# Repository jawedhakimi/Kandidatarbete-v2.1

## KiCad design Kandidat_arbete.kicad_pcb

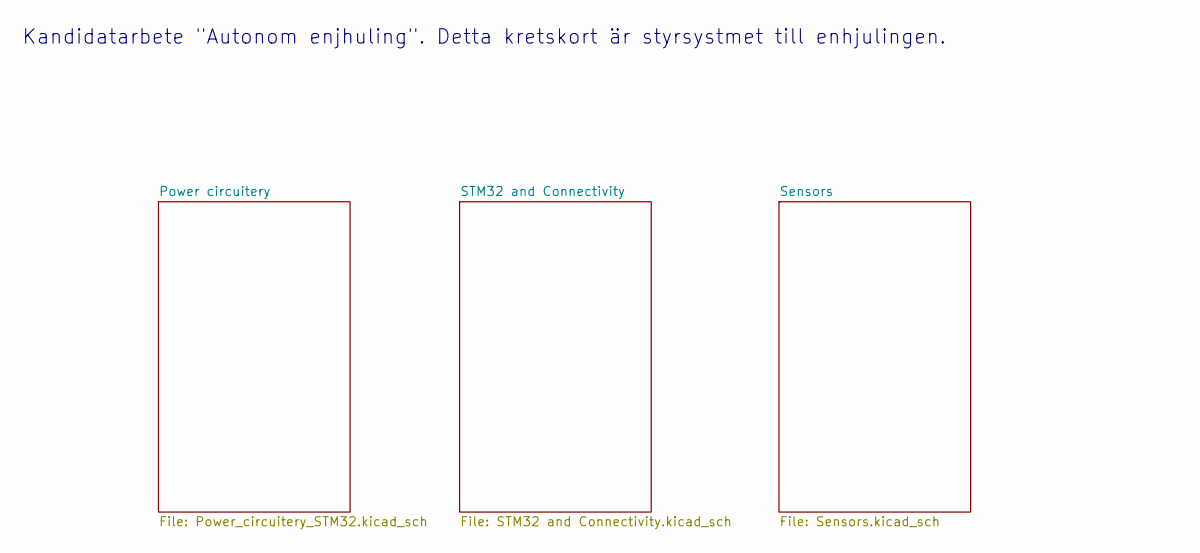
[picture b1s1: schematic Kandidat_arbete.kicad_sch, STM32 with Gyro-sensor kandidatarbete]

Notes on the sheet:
Kandidatarbete "Autonom enjhuling". Detta kretskort är styrsystmet till enhjulingen.

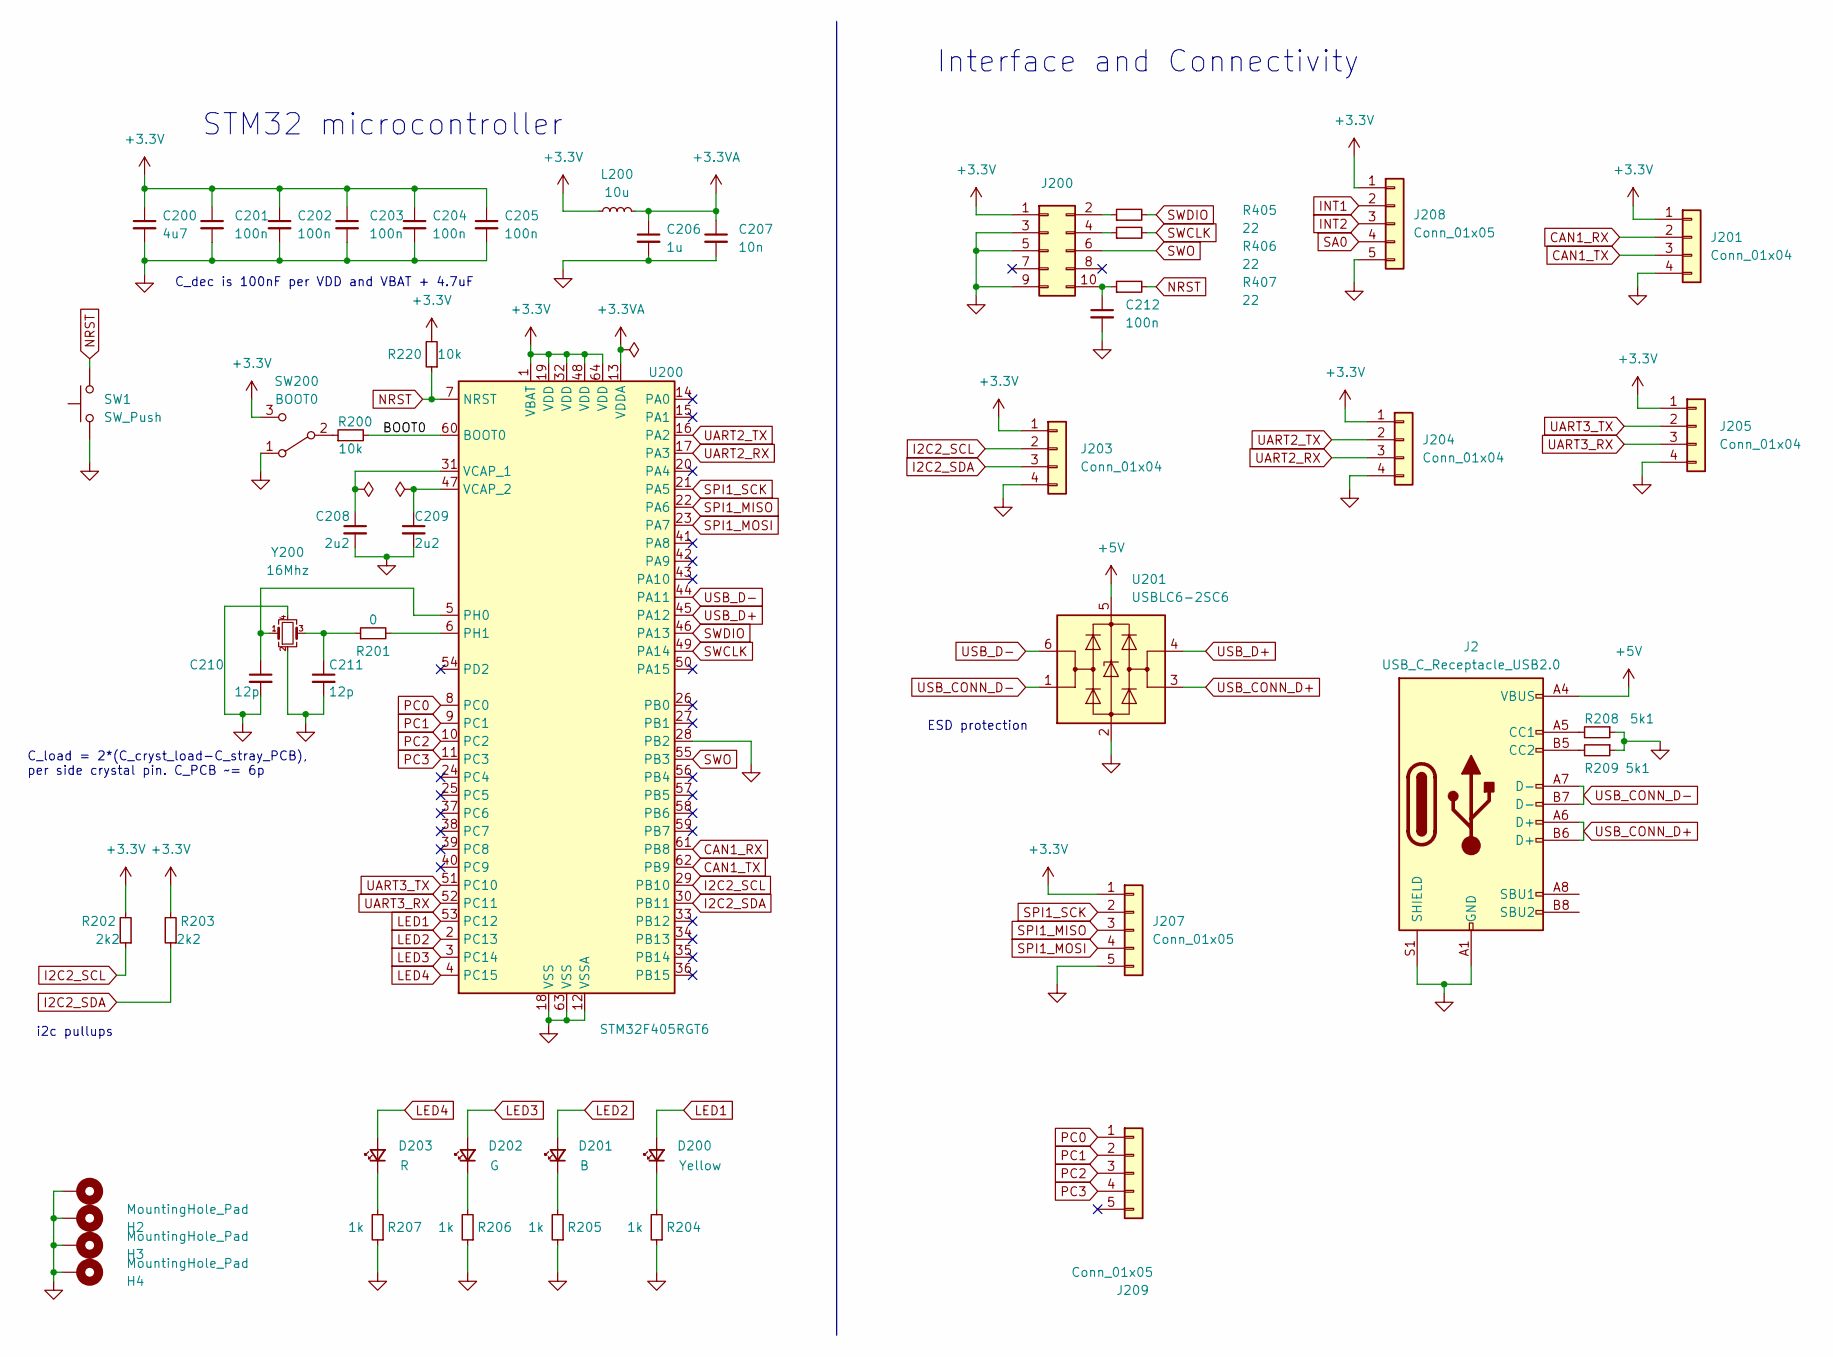
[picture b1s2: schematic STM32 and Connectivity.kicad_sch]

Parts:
C200: 4u7; C_0805_2012Metric; PARTREV C29823; JLC C29823
C201, C202, C203, C204, C205, C212: 100n; C_0805_2012Metric; PARTREV C14663
C206: 1u; C_0805_2012Metric; PARTREV C15849
C207: 10n; C_0805_2012Metric; PARTREV C57112
C208, C209: 2u2; C_0603_1608Metric; PARTREV C23630
C210, C211: 12p; C_0805_2012Metric; PARTREV C38523
D200: Yellow; LED_0603_1608Metric; PARTREV C84256
D201: B; LED_0603_1608Metric; PARTREV C84256
D202: G; LED_0603_1608Metric; PARTREV C84256
D203: R; LED_0603_1608Metric; PARTREV C84256
H1, H2, H3, H4: MountingHole_Pad; MountingHole_3.2mm_M3_Pad_Via
J2: USB_C_Receptacle_USB2.0; GCT_USB4105-GF-A
J200: Conn_02x05_Odd_Even; PinSocket_2x05_P2.54mm_Vertical
J201, J203, J204, J205: Conn_01x04; PinSocket_1x04_P2.54mm_Vertical
J207, J208, J209: Conn_01x05; PinSocket_1x05_P2.54mm_Vertical
L200: 10u; L_0805_2012Metric_Pad1.05x1.20mm_HandSolder; PARTREV C1051; Mouser 710-742792151
R200, R220: 10k; R_0603_1608Metric; PARTREV C25804
R201: 0; R_0603_1608Metric; PARTREV C22764
R202, R203: 2k2; R_0603_1608Metric; PARTREV C23162
R204, R205, R206, R207: 1k; R_0603_1608Metric; PARTREV C25804
R208, R209: 5k1; R_0603_1608Metric; PARTREV C25804
R405, R406, R407: 22; R_0603_1608Metric; PARTREV C227717
SW1: SW_Push; SW_SKRPACE010
SW200: BOOT0; SW_SPDT_PCM12
U200: STM32F405RGT6; LQFP-64_10x10mm_P0.5mm; PARTREV C15742; Mouser 511-STM32F405RGT6
U201: USBLC6-2SC6; SOT-23-6; PARTREV C5261088; Mouser 511-USBLC6-2SC6
Y200: 16Mhz; Crystal_SMD_3225-4Pin_3.2x2.5mm; PARTREV C13738; Mouser 815-ASEAIG-16MHZ-CST

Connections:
+3.3V: C200.1, C201.1, C202.1, C203.1, C204.1, C205.1, J200.1, J201.1, J203.1, J204.1, J205.1, J207.1, J208.1, L200.1, R202.2, R203.2, R220.2, SW200.3 (C), U200.1 (VBAT), U200.19 (VDD), U200.32 (VDD), U200.48 (VDD), U200.64 (VDD); also elsewhere on the board
+3.3VA: C206.1, C207.1, L200.2, U200.13 (VDDA)
+5V: J2.A4 (VBUS), J2.A9 (VBUS), J2.B4 (VBUS), J2.B9 (VBUS), U201.5 (VBUS); also elsewhere on the board
/STM32 and Connectivity/BOOT0: R200.2, U200.60 (BOOT0)
CAN1_RX: J201.2, U200.61 (PB8)
CAN1_TX: J201.3, U200.62 (PB9)
GND: C200.2, C201.2, C202.2, C203.2, C204.2, C205.2, C206.2, C207.2, C208.2, C209.2, C210.2, C211.2, C212.2, H1.1, H2.1, H3.1, H4.1, J2.A1 (GND), J2.A12 (GND), J2.B1 (GND), J2.B12 (GND), J2.S1 (SHIELD), J200.3, J200.5, J200.9, J201.4, J203.4, J204.4, J205.4, J207.5, J208.5, R204.1, R205.1, R206.1, R207.1, R208.1, R209.1, SW1.1, SW200.1 (A), U200.12 (VSSA), U200.18 (VSS), U200.28 (PB2), U200.63 (VSS), U201.2 (GND), Y200.2, Y200.4; also elsewhere on the board
I2C2_SCL: J203.2, R202.1, U200.29 (PB10); also elsewhere on the board
I2C2_SDA: J203.3, R203.1, U200.30 (PB11); also elsewhere on the board
INT1: J208.2; also elsewhere on the board
INT2: J208.3; also elsewhere on the board
LED1: D200.2 (A), U200.53 (PC12)
LED2: D201.2 (A), U200.2 (PC13)
LED3: D202.2 (A), U200.3 (PC14)
LED4: D203.2 (A), U200.4 (PC15)
NRST: R220.1, R407.2, SW1.2, U200.7 (NRST)
unnamed: C208.1, U200.31 (VCAP_1)
unnamed: C209.1, U200.47 (VCAP_2)
unnamed: C211.1, R201.1, Y200.3
unnamed: D200.1 (K), R204.2
unnamed: D201.1 (K), R205.2
unnamed: D202.1 (K), R206.2
unnamed: D203.1 (K), R207.2
unnamed: J2.A5 (CC1), R208.2
unnamed: J2.B5 (CC2), R209.2
unnamed: J200.2, R405.1
unnamed: J200.4, R406.1
unnamed: C212.1, J200.10, R407.1
unnamed: R200.1, SW200.2 (B)
unnamed: C210.1, U200.5 (PH0), Y200.1
unnamed: R201.2, U200.6 (PH1)
PC0: J209.1, U200.8 (PC0)
PC1: J209.2, U200.9 (PC1)
PC2: J209.3, U200.10 (PC2)
PC3: J209.4, U200.11 (PC3)
SA0: J208.4; also elsewhere on the board
SPI1_MISO: J207.3, U200.22 (PA6)
SPI1_MOSI: J207.4, U200.23 (PA7)
SPI1_SCK: J207.2, U200.21 (PA5)
SWCLK: R406.2, U200.49 (PA14)
SWDIO: R405.2, U200.46 (PA13)
SWO: J200.6, U200.55 (PB3)
UART2_RX: J204.3, U200.17 (PA3)
UART2_TX: J204.2, U200.16 (PA2)
UART3_RX: J205.3, U200.52 (PC11)
UART3_TX: J205.2, U200.51 (PC10)
USB_CONN_D+: J2.A6 (D+), J2.B6 (D+), U201.3 (I/O2)
USB_CONN_D-: J2.A7 (D-), J2.B7 (D-), U201.1 (I/O1)
USB_D+: U200.45 (PA12), U201.4 (I/O2)
USB_D-: U200.44 (PA11), U201.6 (I/O1)

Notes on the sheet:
Interface and Connectivity
i2c pullups
C_load = 2*(C_cryst_load-C_stray_PCB), per side crystal pin. C_PCB ~= 6p
ESD protection
STM32 microcontroller
C_dec is 100nF per VDD and VBAT + 4.7uF

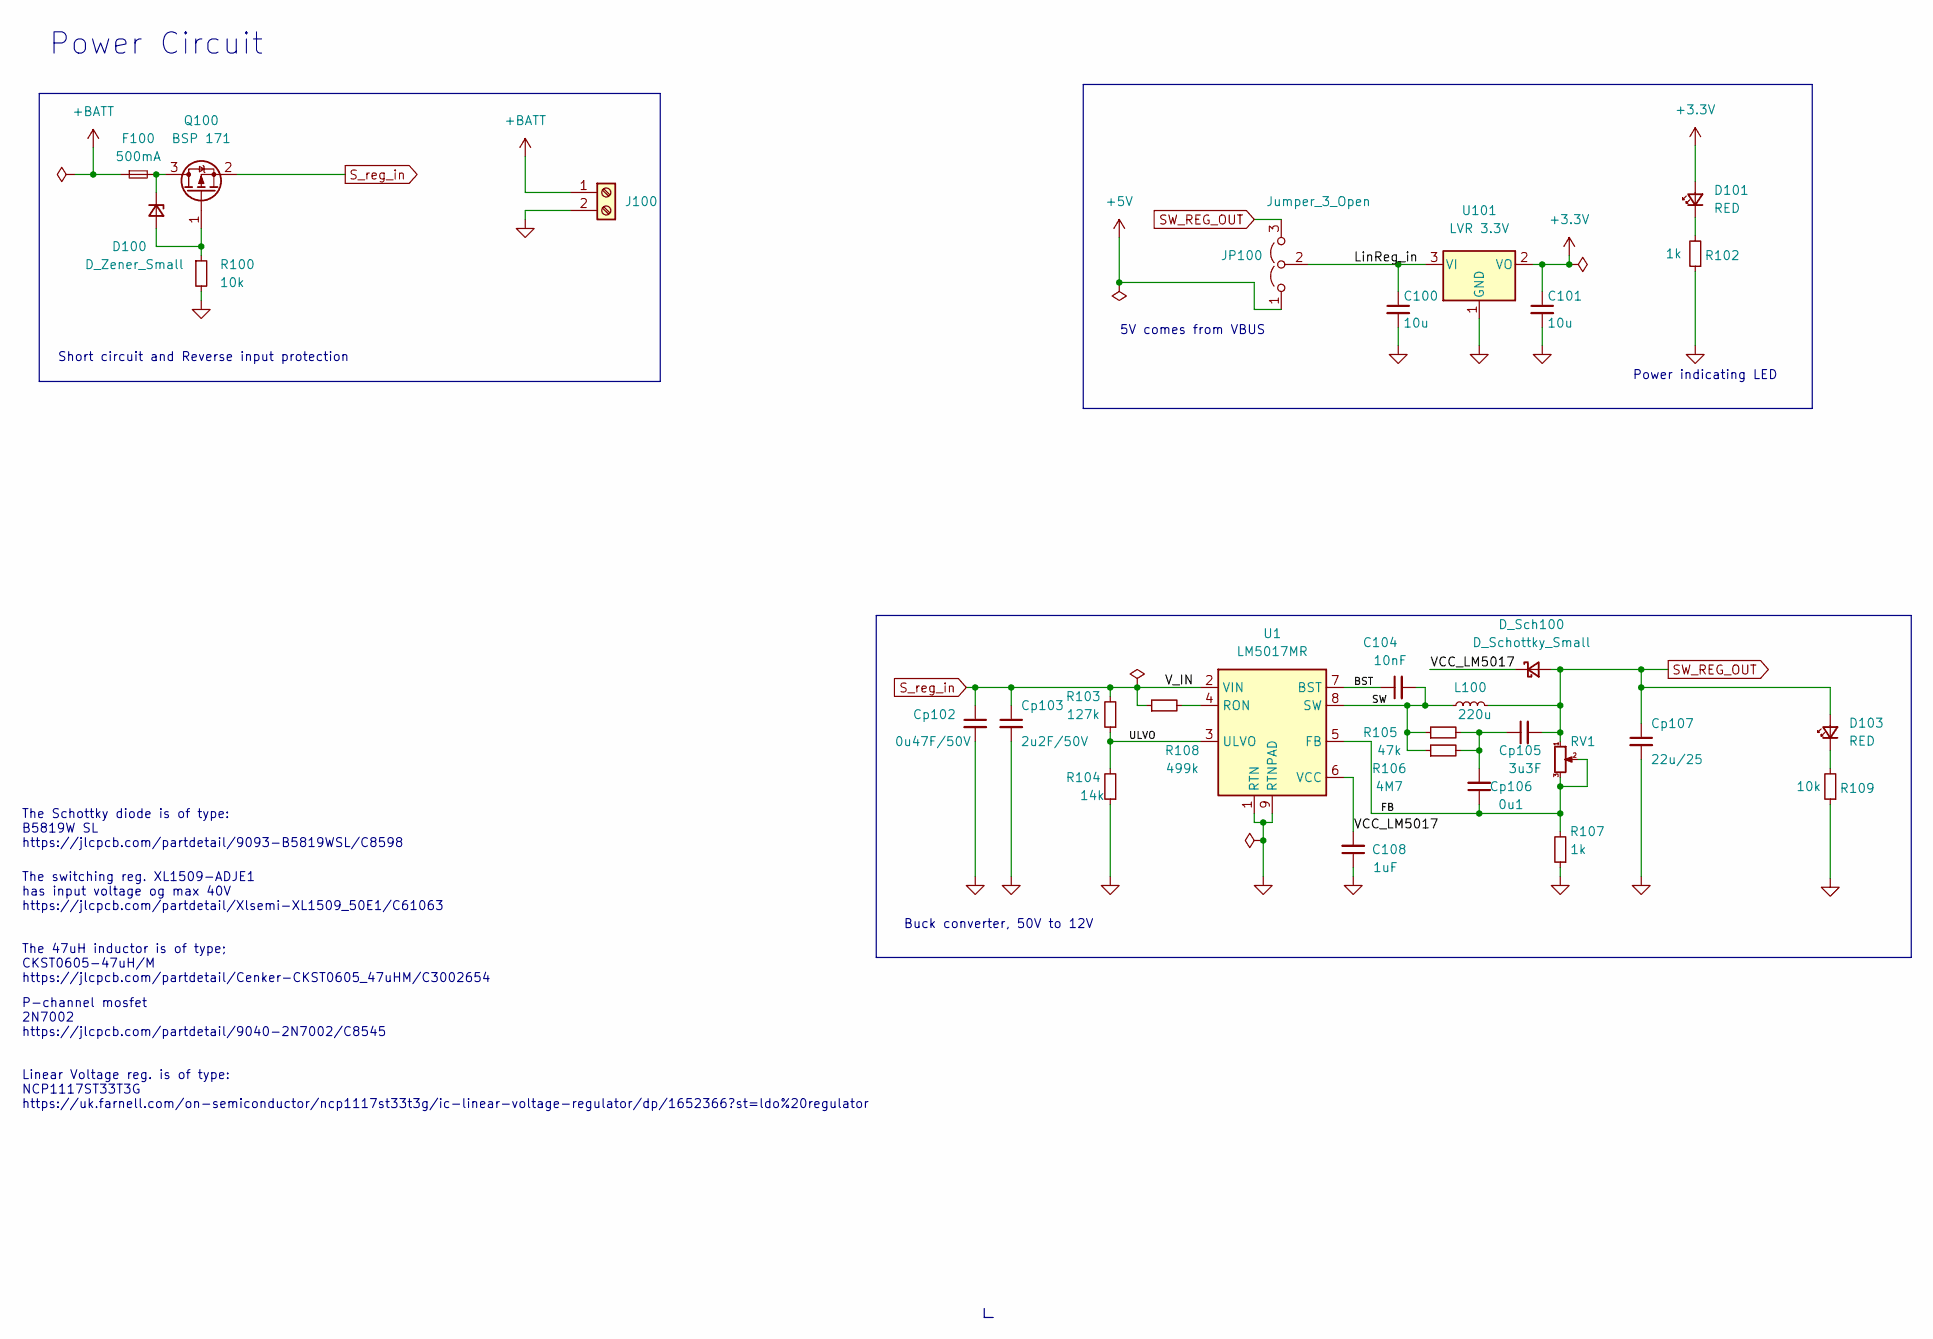
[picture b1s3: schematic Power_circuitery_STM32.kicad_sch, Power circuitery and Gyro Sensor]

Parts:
C100, C101: 10u; C_0805_2012Metric; PARTREV C96446; JLC C96446
C104: 10nF; C_0805_2012Metric; PARTREV C57112
C108: 1uF; C_0805_2012Metric; PARTREV C28323
Cp102: 0u47F/50V; C_0805_2012Metric; PARTREV C13967
Cp103: 2u2F/50V; C_0805_2012Metric; PARTREV C49217
Cp105: 3u3F; C_0805_2012Metric; PARTREV C338093
Cp106: 0u1; C_0805_2012Metric; PARTREV C14663
Cp107: 22u/25; C_0805_2012Metric_Pad1.18x1.45mm_HandSolder; PARTREV C45783
D100: D_Zener_Small; R_Axial_DIN0204_L3.6mm_D1.6mm_P5.08mm_Vertical; PARTREV C8062
D101, D103: RED; LED_0603_1608Metric; PARTREV C84256
D_Sch100: D_Schottky_Small; TO-277; PARTREV C8678; Mouser 637-SK35SMA
F100: 500mA; R_Axial_DIN0204_L3.6mm_D1.6mm_P5.08mm_Vertical; PARTREV C8678
J100: Screw_Terminal_01x02; TerminalBlock_Philmore_TB132_1x02_P5.00mm_Horizontal
JP100: Jumper_3_Open; PinHeader_1x03_P2.54mm_Vertical
L100: 220u; L_Bourns_SRR1208_12.7x12.7mm; PARTREV C2929503; Mouser 652-SRR1208-221KL
Q100: BSP 171; bsp171; PARTREV C15127; Mouser 726-BSP171PH6327
R100: 10k; R_0603_1608Metric; PARTREV C25804
R102: 1k; R_0603_1608Metric; PARTREV C22764
R103: 127k; R_0603_1608Metric; PARTREV C25804
R104: 14k; R_0603_1608Metric; PARTREV C25804
R105: 47k; R_0603_1608Metric; PARTREV C25804
R106: 4M7; R_0603_1608Metric; PARTREV C25804
R107: 1k; R_0603_1608Metric; PARTREV C25804
R108: 499k; R_0603_1608Metric; PARTREV C25804
R109: 10k; R_0603_1608Metric; PARTREV C22764
RV1: R_Potentiometer_Small; TRIM_TC33X-2-103E
U1: LM5017MR; SOIC-8-1EP_3.9x4.9mm_P1.27mm_EP2.95x4.9mm_Mask2.71x3.4mm_Th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; PARTREV C34355; Mouser 926-LM5017MRX/NOPB
U101: LVR 3.3V; SOT-223-3_TabPin2; PARTREV C277892; Mouser 584-ADP3338AKCZ3.3R

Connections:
+3.3V: C101.1, D101.2 (A), U101.2 (VO); also elsewhere on the board
+5V: JP100.1 (A); also elsewhere on the board
+BATT: F100.1, J100.1
/Power circuitery/BST: C104.1, U1.7 (BST)
/Power circuitery/FB: Cp106.1, R107.2, RV1.2, RV1.3, U1.5 (FB)
/Power circuitery/LinReg_in: C100.1, JP100.2 (C), U101.3 (VI)
/Power circuitery/SW: C104.2, L100.1, R105.1, R106.1, U1.8 (SW)
/Power circuitery/ULVO: R103.1, R104.2, U1.3 (ULVO)
/Power circuitery/VCC_LM5017: C108.2, D_Sch100.3 (K), U1.6 (VCC)
GND: C100.2, C101.2, C108.1, Cp102.2, Cp103.2, Cp107.2, J100.2, R100.2, R102.1, R104.1, R107.1, R109.1, U1.1 (RTN), U1.9 (RTNPAD), U101.1 (GND); also elsewhere on the board
unnamed: Cp105.1, Cp106.2, R105.2, R106.2
unnamed: D100.2 (A), Q100.1 (G), R100.1
unnamed: D100.1 (K), F100.2, Q100.3 (D)
unnamed: D101.1 (K), R102.2
unnamed: D103.1 (K), R109.2
unnamed: R108.2, U1.4 (RON)
SW_REG_OUT: Cp105.2, Cp107.1, D103.2 (A), D_Sch100.1 (A), D_Sch100.2 (A), JP100.3 (B), L100.2, RV1.1
S_reg_in: Cp102.1, Cp103.1, Q100.2 (S), R103.2, R108.1, U1.2 (VIN)

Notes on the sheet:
Buck converter, 50V to 12V
5V comes from VBUS
Power Circuit
The Schottky diode is of type: B5819W SL https://jlcpcb.com/partdetail/9093-B5819WSL/C8598
The switching reg. XL1509-ADJE1 has input voltage og max 40V https://jlcpcb.com/partdetail/Xlsemi-XL1509_50E1/C61063
Linear Voltage reg. is of type: NCP1117ST33T3G https://uk.farnell.com/on-semiconductor/ncp1117st33t3g/ic-linear-voltage-regulator/dp/1652366?st=ldo%20regulator
Power indicating LED
Short circuit and Reverse input protection
P-channel mosfet 2N7002 https://jlcpcb.com/partdetail/9040-2N7002/C8545
The 47uH inductor is of type; CKST0605-47uH/M https://jlcpcb.com/partdetail/Cenker-CKST0605_47uHM/C3002654

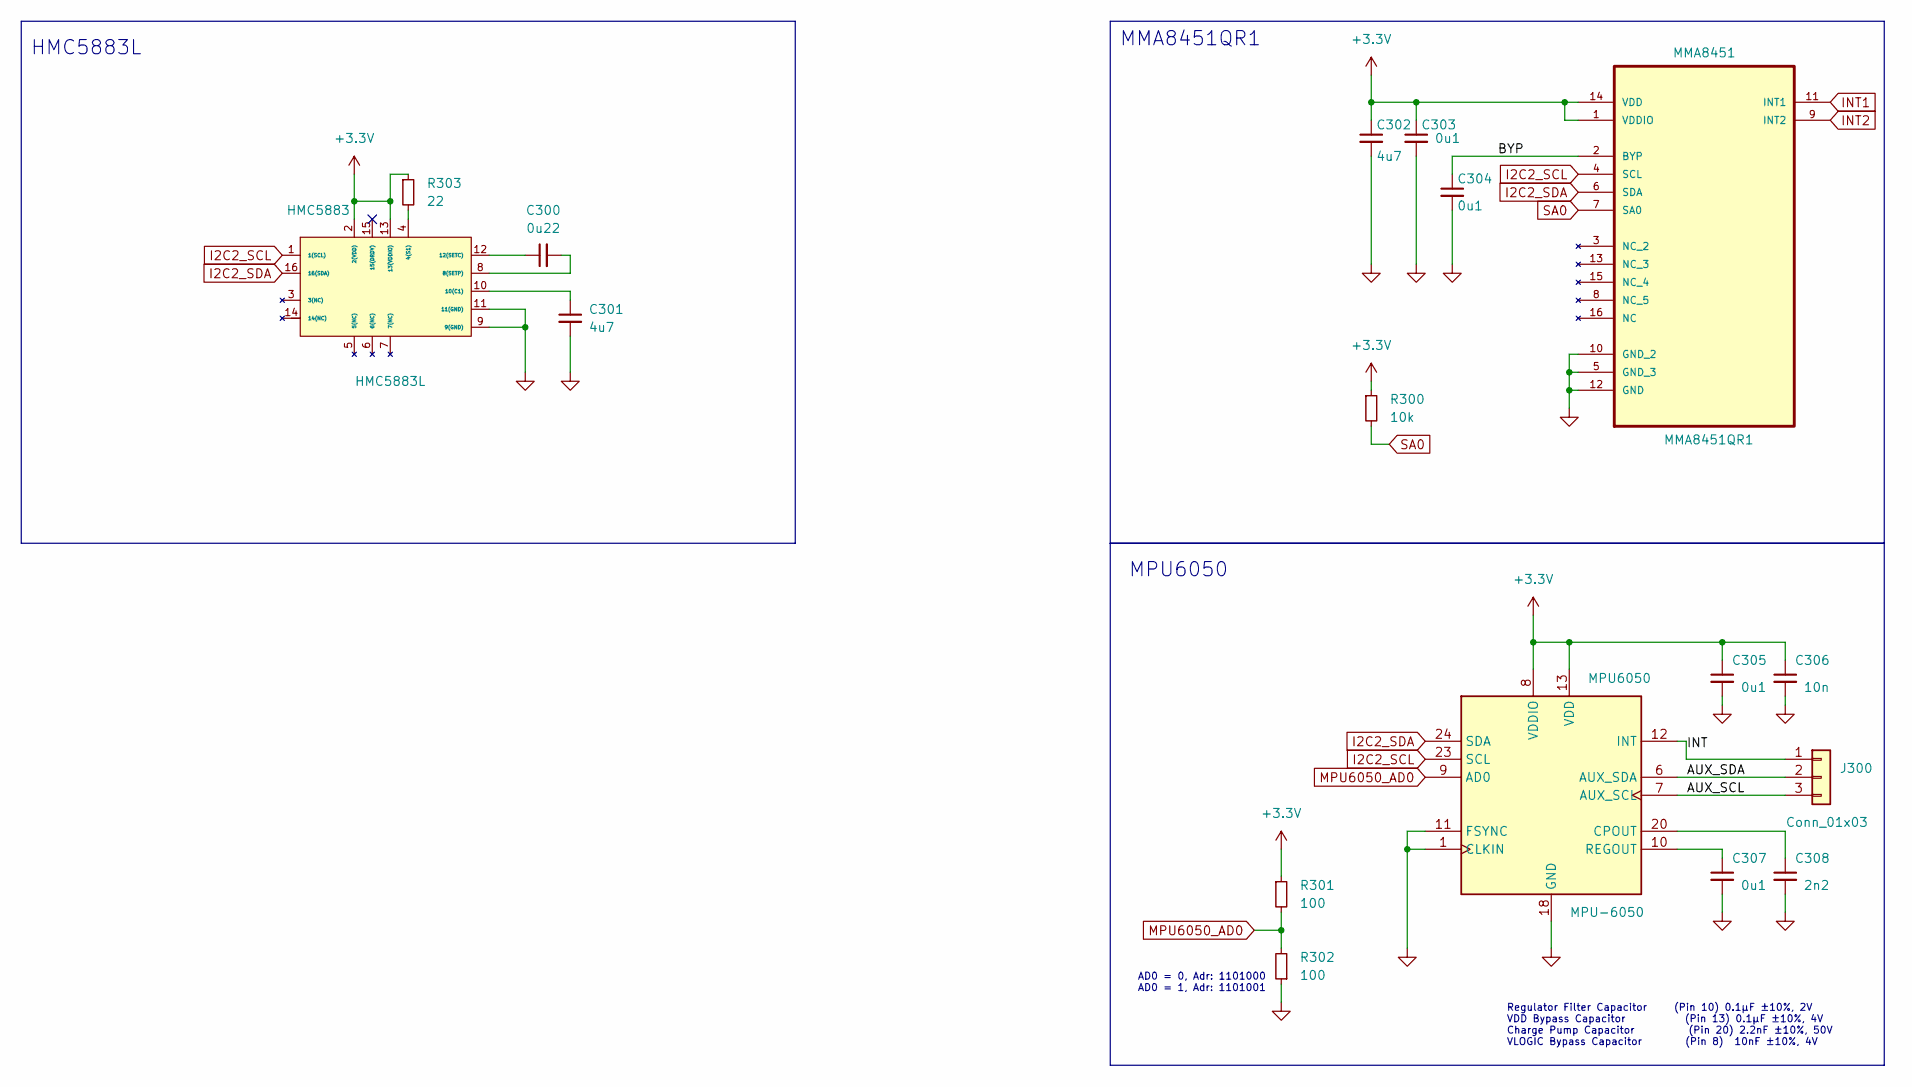
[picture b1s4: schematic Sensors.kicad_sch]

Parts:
C300: 0u22; C_0805_2012Metric; PARTREV C21122
C301: 4u7; C_0805_2012Metric; PARTREV C29823
C302: 4u7; C_0805_2012Metric; PARTREV C29823; JLC C29823
C303, C304, C305, C307: 0u1; C_0805_2012Metric; PARTREV C14663
C306: 10n; C_0805_2012Metric; PARTREV C57112
C308: 2n2; C_0805_2012Metric; PARTREV C1604
HMC5883: HMC5883L; PLCC16-0.5-3X3MM; MPN HMC5883L
J300: Conn_01x03; PinHeader_1x03_P2.54mm_Vertical
MMA8451: MMA8451QR1; QFN50P300X300X100-16N; MPN MMA8451QR1
MPU6050: MPU-6050; InvenSense_QFN-24_4x4mm_P0.5mm; PARTREV C24112; Mouser 410-MPU-6050
R300: 10k; R_0603_1608Metric; PARTREV C25804
R301, R302: 100; R_0603_1608Metric; PARTREV C22775
R303: 22; R_0603_1608Metric; PARTREV C25804

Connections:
+3.3V: C302.1, C303.1, C305.1, C306.1, HMC5883.2 (2(VDD)), HMC5883.13 (13(VDDIO)), MMA8451.1 (VDDIO), MMA8451.14 (VDD), MPU6050.8 (VDDIO), MPU6050.13 (VDD), R300.1, R301.1, R303.1; also elsewhere on the board
/Sensors/AUX_SCL: J300.3, MPU6050.7 (AUX_SCL)
/Sensors/AUX_SDA: J300.2, MPU6050.6 (AUX_SDA)
/Sensors/BYP: C304.1, MMA8451.2 (BYP)
/Sensors/INT: J300.1, MPU6050.12 (INT)
GND: C301.2, C302.2, C303.2, C304.2, C305.2, C306.2, C307.2, C308.2, HMC5883.9 (9(GND)), HMC5883.11 (11(GND)), MMA8451.5 (GND_3), MMA8451.10 (GND_2), MMA8451.12 (GND), MPU6050.1 (CLKIN), MPU6050.11 (FSYNC), MPU6050.18 (GND), R302.1; also elsewhere on the board
I2C2_SCL: HMC5883.1 (1(SCL)), MMA8451.4 (SCL), MPU6050.23 (SCL); also elsewhere on the board
I2C2_SDA: HMC5883.16 (16(SDA)), MMA8451.6 (SDA), MPU6050.24 (SDA); also elsewhere on the board
INT1: MMA8451.11 (INT1); also elsewhere on the board
INT2: MMA8451.9 (INT2); also elsewhere on the board
MPU6050_AD0: MPU6050.9 (AD0), R301.2, R302.2
unnamed: HMC5883.4 (4(S1)), R303.2
unnamed: C300.2, HMC5883.8 (8(SETP))
unnamed: C301.1, HMC5883.10 (10(C1))
unnamed: C300.1, HMC5883.12 (12(SETC))
unnamed: C308.1, MPU6050.20 (CPOUT)
unnamed: C307.1, MPU6050.10 (REGOUT)
SA0: MMA8451.7 (SA0), R300.2; also elsewhere on the board

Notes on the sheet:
AD0 = 0, Adr: 1101000 AD0 = 1, Adr: 1101001
MPU6050
MMA8451QR1
HMC5883L
Regulator Filter Capacitor (Pin 10) 0.1µF ±10%, 2V VDD Bypass Capacitor (Pin 13) 0.1µF ±10%, 4V Charge Pump Capacitor (Pin 20) 2.2nF ±10%, 50V VLOGIC Bypass Capacitor (Pin 8) 10nF ±10%, 4V

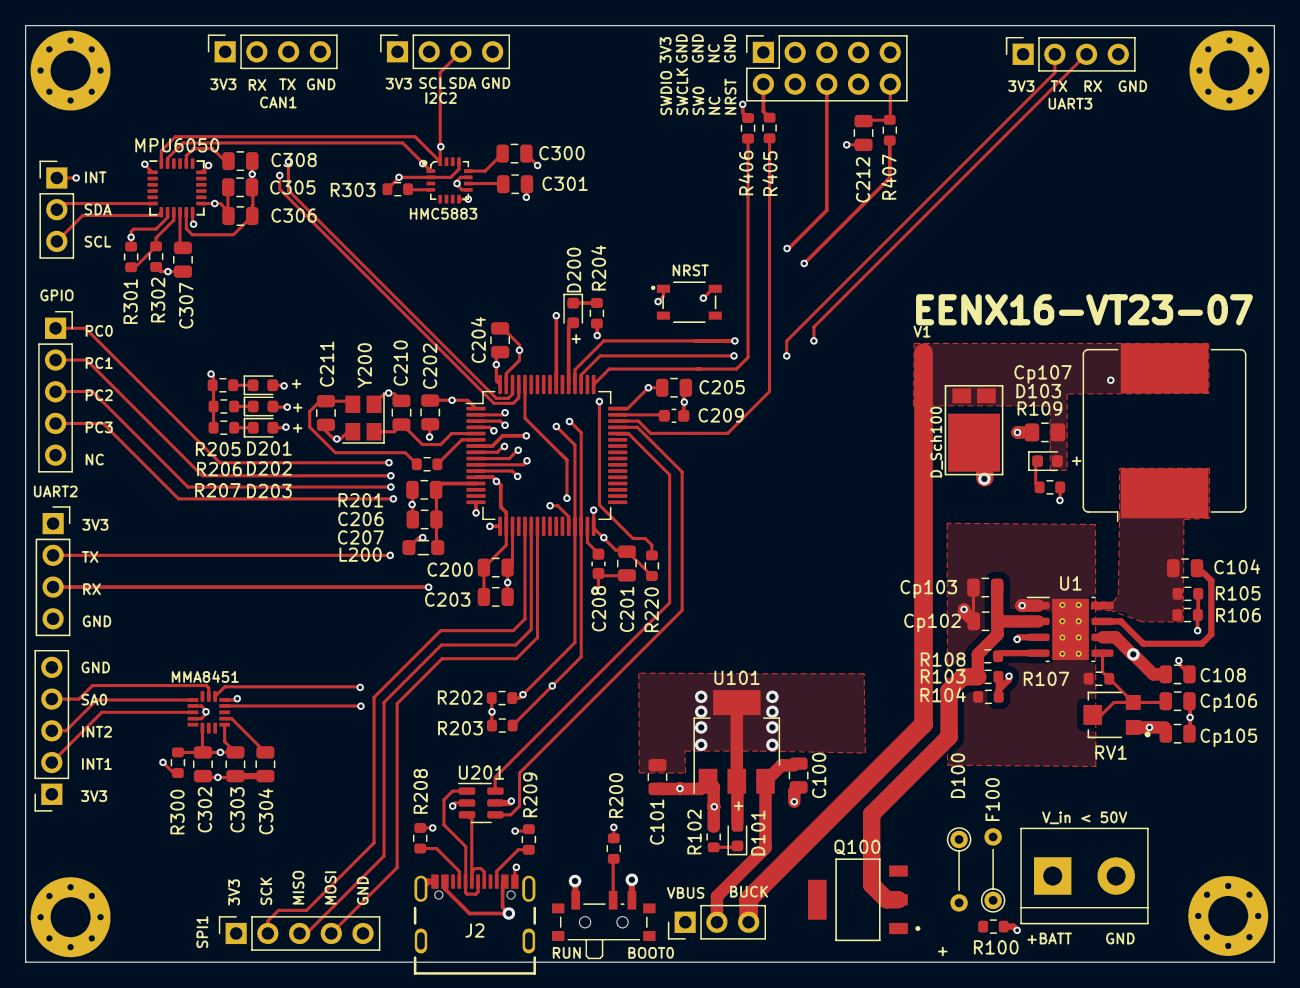
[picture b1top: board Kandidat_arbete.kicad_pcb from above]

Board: 4 copper layers, 100.0 x 75.0 mm, 97 parts (0 on the bottom side), 76 nets.

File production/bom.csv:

Designator,Footprint,Quantity,Value,LCSC Part #
C100,0805,1,10u,C96446
C101,0805,1,10u,C96446
C104,0805,1,10nF,
C108,0805,1,1uF,
C200,0805,1,4u7,C29823
C201,0805,1,100n,
C202,0805,1,100n,
C203,0805,1,100n,
C204,0805,1,100n,
C205,0805,1,100n,
C206,0805,1,1u,
C207,0805,1,10n,
C208,0603,1,2u2,
C209,0603,1,2u2,
C210,0805,1,12p,
C211,0805,1,12p,
C212,0805,1,100n,
C300,0805,1,0u22,
C301,0805,1,4u7,
C302,0805,1,4u7,C29823
C303,0805,1,0u1,
C304,0805,1,0u1,
C305,0805,1,0u1,
C306,0805,1,10n,
C307,0805,1,0u1,
C308,0805,1,2n2,
Cp102,0805,1,0u47F/50V,
Cp103,0805,1,2u2F/50V,
Cp105,0805,1,3u3F,
Cp106,0805,1,0u1,
Cp107,0805,1,22u/25,
D100,D_SMA,1,D_Zener_Small,
D101,0603,1,RED,
D103,0603,1,RED,
D200,0603,1,Yellow,
D201,0603,1,B,
D202,0603,1,G,
D203,0603,1,R,
D_Sch100,TO-277,1,D_Schottky_Small,
F100,R_Axial_DIN0204_L3.6mm_D1.6mm_P5.08mm_Vertical,1,500mA,
"H1, H2, H3, H4",MountingHole_3.2mm_M3_Pad_Via,4,MountingHole_Pad,
HMC5883,PLCC16-0.5-3X3MM,1,HMC5883L,
J100,TerminalBlock_bornier-2_P5.08mm,1,Screw_Terminal_01x02,
J200,PinSocket_2x05_P2.54mm_Vertical,1,Conn_02x05_Odd_Even,
"J201, J203, J204, J205",PinSocket_1x04_P2.54mm_Vertical,4,Conn_01x04,
"J207, J208, J209",PinSocket_1x05_P2.54mm_Vertical,3,Conn_01x05,
J300,PinHeader_1x03_P2.54mm_Vertical,1,Conn_01x03,
JP100,PinHeader_1x03_P2.54mm_Vertical,1,Jumper_3_Open,
L100,L_Bourns_SRR1208_12.7x12.7mm,1,220u,
L200,0805,1,10u,
MMA8451,QFN50P300X300X100-16N,1,MMA8451QR1,
MPU6050,InvenSense_QFN-24_4x4mm_P0.5mm,1,MPU-6050,
Q100,bsp171,1,BSP 171,
R100,0603,1,10k,
R102,0603,1,1k,
R103,0603,1,127k,
R104,0603,1,14k,
R105,0603,1,47k,
R106,0603,1,4M7,
R107,0603,1,1k,
R108,0603,1,499k,
R109,0603,1,10k,
R200,0603,1,10k,
R201,0603,1,0,
R202,0603,1,2k2,
R203,0603,1,2k2,
R204,0603,1,1k,
R205,0603,1,1k,
R206,0603,1,1k,
R207,0603,1,1k,
R208,0603,1,5k1,
R209,0603,1,5k1,
R220,0603,1,10k,
R300,0603,1,10k,
R301,0603,1,100,
R302,0603,1,100,
R303,0603,1,22,
R405,0603,1,22,
R406,0603,1,22,
R407,0603,1,22,
RV1,TRIM_TC33X-2-103E,1,R_Potentiometer_Small,
SW200,SW_SPDT_PCM12,1,BOOT0,
U1,SOIC-8-1EP_3.9x4.9mm_P1.27mm_EP2.95x4.9mm_Mask2.71x3.4mm_ThermalVias,1,LM5017MR,
U101,SOT-223-3_TabPin2,1,LVR 3.3V,
U200,LQFP-64_10x10mm_P0.5mm,1,STM32F405RGT6,
U201,SOT-23-6,1,USBLC6-2SC6,
USB_C1,JAE_DX07S016JA1R1500,1,USB_C_receptacle,
Y200,Crystal_SMD_3225-4Pin_3.2x2.5mm,1,16Mhz,

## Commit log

2023-04-23 ny mapp skapades med ny aändringar
2023-04-23 Revert "changes"
    This reverts commit 655f2439946f26e228e6387e4a45df3a138819d6.
